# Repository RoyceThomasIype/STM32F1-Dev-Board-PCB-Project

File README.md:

# STM32 F103 Development Board

A custom PCB for the STM32F103C8T6 microcontroller with exposed I2C, and UART peripherals.

The PCB can be used to analyze I2C and UART communication of the MCU and also have SWD pins to program the board.

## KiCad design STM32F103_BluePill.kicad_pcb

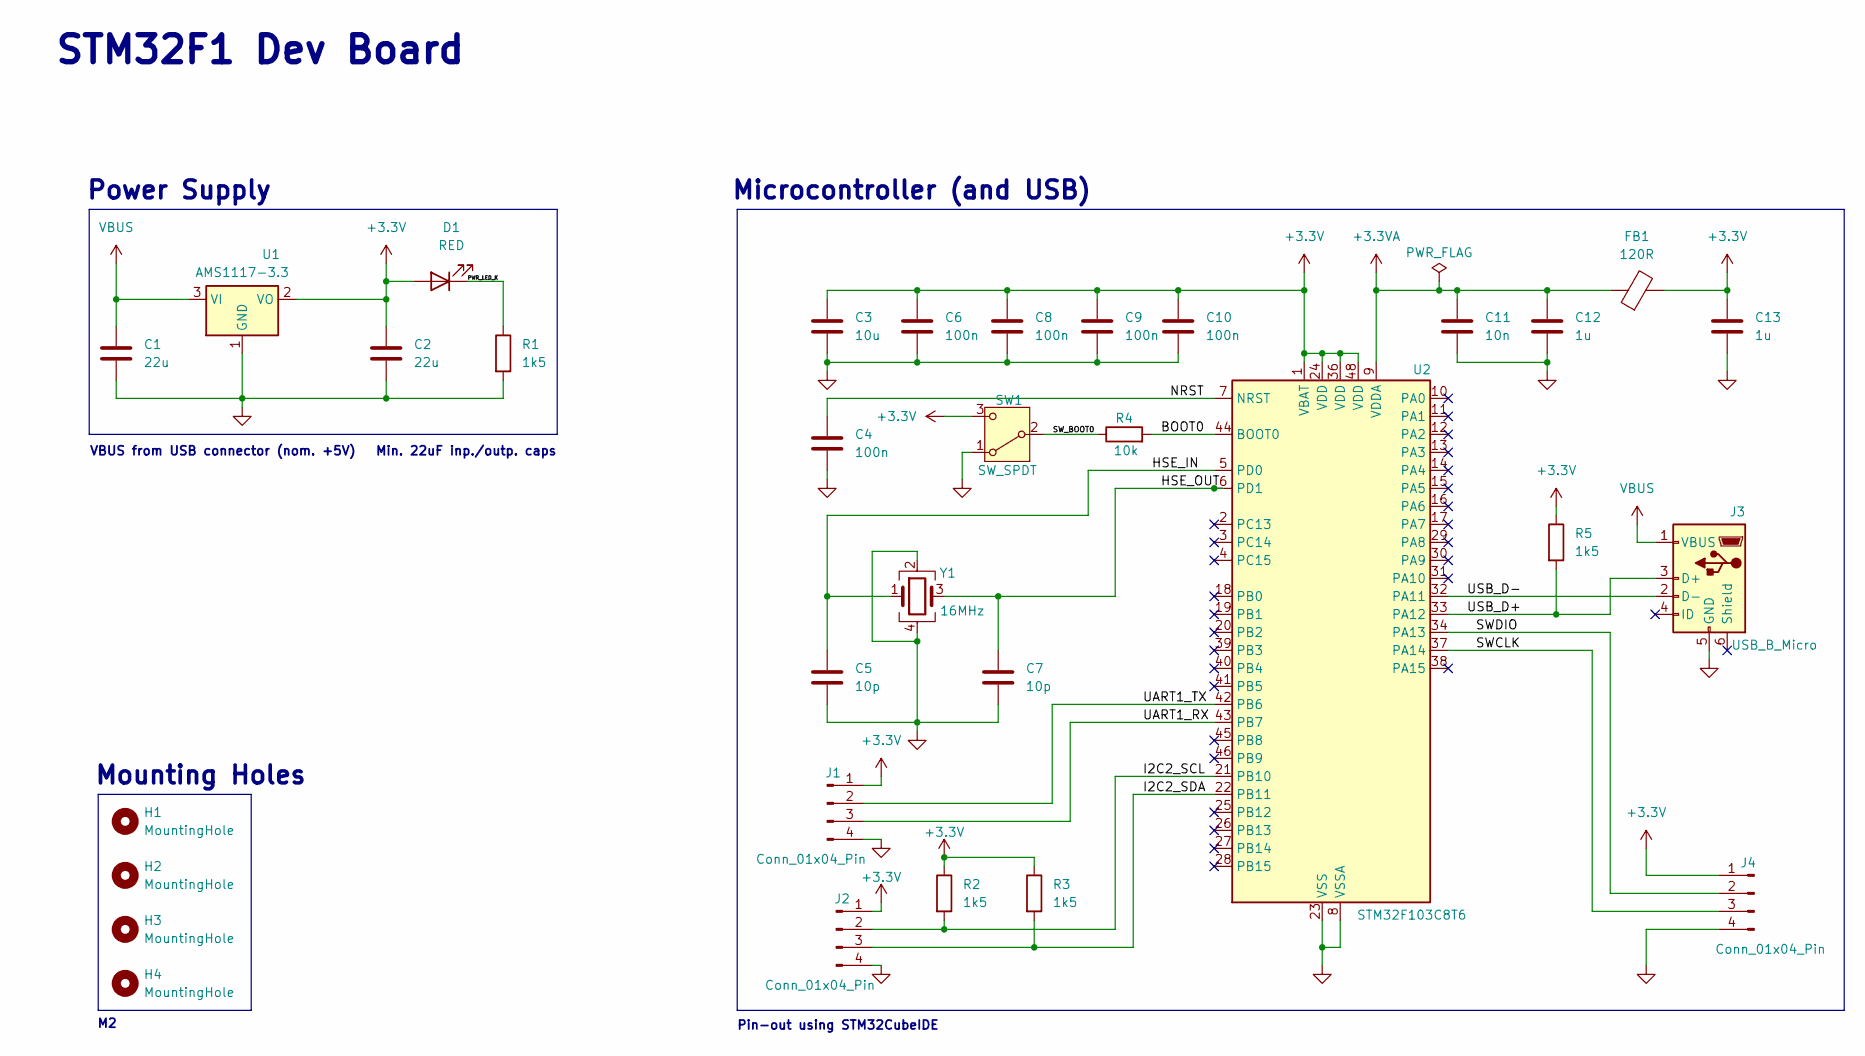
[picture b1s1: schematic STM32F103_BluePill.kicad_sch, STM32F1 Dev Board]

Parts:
C1, C2: 22u; C_0805_2012Metric
C3: 10u; C_0603_1608Metric
C4, C6, C8, C9, C10: 100n; C_0402_1005Metric
C5, C7: 10p; C_0402_1005Metric
C11: 10n; C_0402_1005Metric
C12, C13: 1u; C_0402_1005Metric
D1: RED; LED_0603_1608Metric
FB1: 120R; L_0603_1608Metric
H1, H2, H3, H4: MountingHole; MountingHole_2.2mm_M2
J1, J2, J4: Conn_01x04_Pin; PinHeader_1x04_P2.54mm_Vertical
J3: USB_B_Micro; USB_Micro-B_Wuerth_629105150521
R1, R2, R3, R5: 1k5; R_0402_1005Metric
R4: 10k; R_0402_1005Metric
SW1: SW_SPDT; SW_SPDT_PCM12
U1: AMS1117-3.3; SOT-223-3_TabPin2
U2: STM32F103C8T6; LQFP-48_7x7mm_P0.5mm
Y1: 16MHz; Crystal_SMD_3225-4Pin_3.2x2.5mm

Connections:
+3.3V: C2.1, C3.1, C6.1, C8.1, C9.1, C10.1, C13.1, D1.2 (A), FB1.2, J1.1, J2.1, J4.1, R2.1, R3.1, R5.1, SW1.3 (C), U1.2 (VO), U2.1 (VBAT), U2.24 (VDD), U2.36 (VDD), U2.48 (VDD)
+3.3VA: C11.1, C12.1, FB1.1, U2.9 (VDDA)
/BOOT0: R4.2, U2.44 (BOOT0)
/HSE_IN: C5.1, U2.5 (PD0), Y1.1
/HSE_OUT: C7.1, U2.6 (PD1), Y1.3
/I2C2_SCL: J2.2, R2.2, U2.21 (PB10)
/I2C2_SDA: J2.3, R3.2, U2.22 (PB11)
/NRST: C4.1, U2.7 (NRST)
/PWR_LED_K: D1.1 (K), R1.1
/SWCLK: J4.3, U2.37 (PA14)
/SWDIO: J4.2, U2.34 (PA13)
/SW_BOOT0: R4.1, SW1.2 (B)
/UART1_RX: J1.3, U2.43 (PB7)
/UART1_TX: J1.2, U2.42 (PB6)
/USB_D+: J3.3 (D+), R5.2, U2.33 (PA12)
/USB_D-: J3.2 (D-), U2.32 (PA11)
GND: C1.2, C2.2, C3.2, C4.2, C5.2, C6.2, C7.2, C8.2, C9.2, C10.2, C11.2, C12.2, C13.2, J1.4, J2.4, J3.5 (GND), J4.4, R1.2, SW1.1 (A), U1.1 (GND), U2.8 (VSSA), U2.23 (VSS), U2.35 (VSS), U2.47 (VSS), Y1.2, Y1.4
VBUS: C1.1, J3.1 (VBUS), U1.3 (VI)

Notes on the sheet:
Microcontroller (and USB)
Power Supply
STM32F1 Dev Board
Mounting Holes
VBUS from USB connector (nom. +5V) Min. 22uF inp./outp. caps
Pin-out using STM32CubeIDE

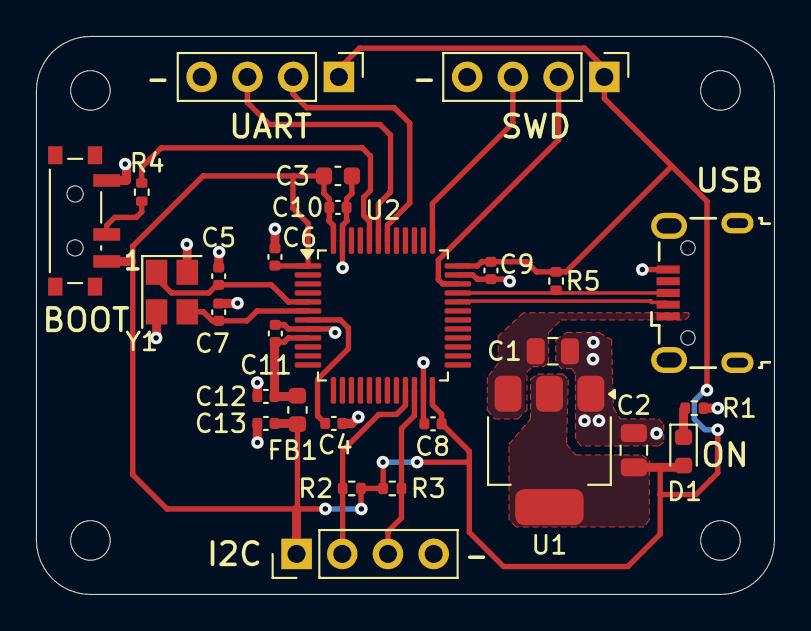
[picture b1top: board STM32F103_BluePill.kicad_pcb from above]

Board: 2 copper layers, 41.0 x 31.0 mm, 32 parts (0 on the bottom side), 18 nets.

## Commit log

2024-03-03 Complteted the schematic
2024-03-16 Completed PCB layout
2024-03-16 Added schematic and layout pdf
2024-03-16 Added README.md
